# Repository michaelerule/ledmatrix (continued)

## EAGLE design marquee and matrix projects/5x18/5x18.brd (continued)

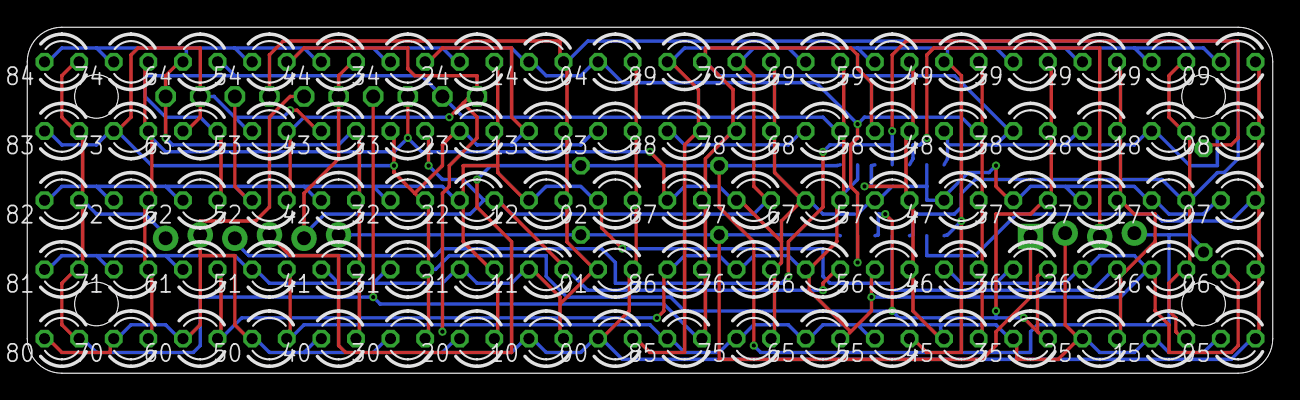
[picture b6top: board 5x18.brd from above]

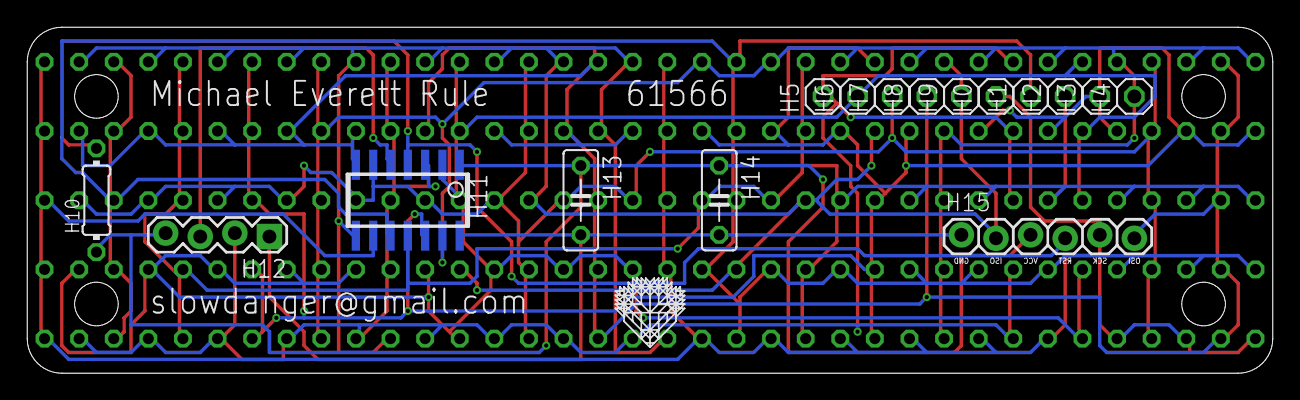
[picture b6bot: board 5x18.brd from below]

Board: 2 copper layers, 91.4 x 25.4 mm, 107 parts (17 on the bottom side), 14 nets.

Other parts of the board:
H16: LOGO

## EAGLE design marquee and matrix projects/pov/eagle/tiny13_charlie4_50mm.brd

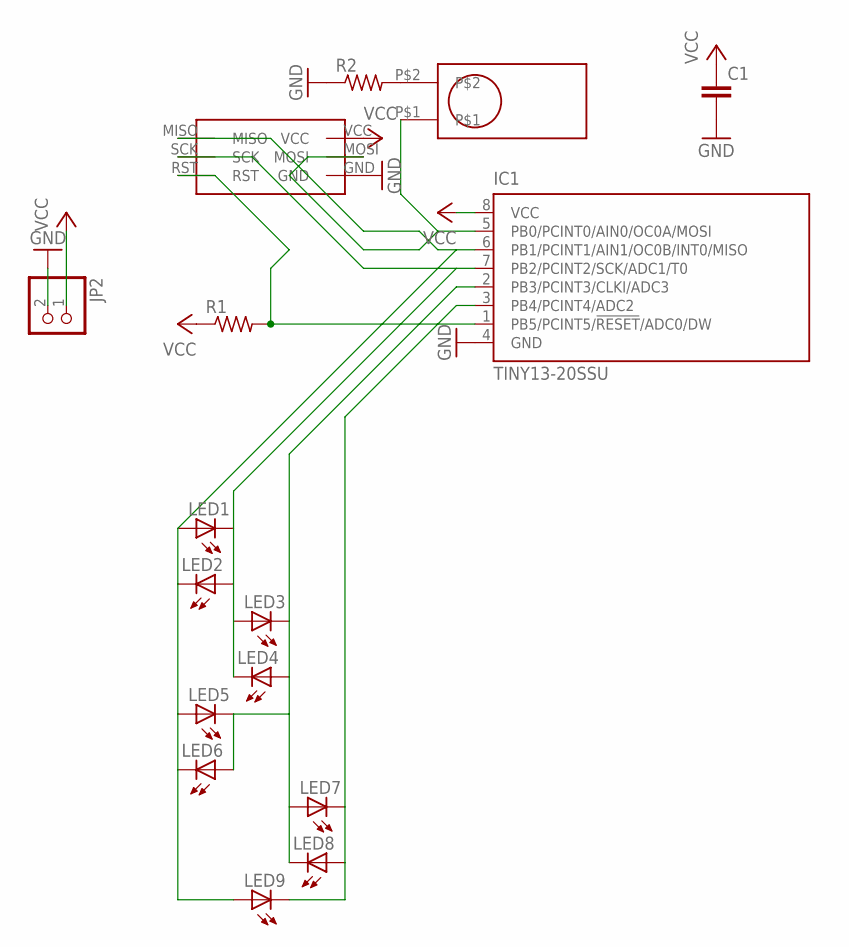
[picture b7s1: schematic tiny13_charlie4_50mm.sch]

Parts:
C1: C-EU025-025X050; C025-025X050
IC1: TINY13-20SSU; 8S1
JP2: PINHD-1X2/90; 1X02/90
LED1, LED2, LED3, LED4, LED5, LED6, LED7, LED8, LED9: LED3MM
R1, R2: R-US_0207/7; 0207/7
U$1: TILT_SWITCH_MECHANICAL
U$2: AVR_ISP_6_PIN_1X6_SMT_CONTACT_PROGRAMMER; CONTACT_ISP_PROGRAMMER_1X6_ATMEL

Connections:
GND: C1.2, IC1.4 (GND), JP2.2, R2.1, U$2.GND
unnamed: IC1.2 (PB3/PCINT3/CLKI/ADC3), LED3.K (C), LED4.A, LED5.K (C), LED6.A, LED7.A, LED8.K (C)
unnamed: IC1.7 (PB2/PCINT2/SCK/ADC1/T0), LED1.K (C), LED2.A, LED3.A, LED4.K (C), U$2.SCK
unnamed: R2.2, U$1.P$2
unnamed: IC1.3 (PB4/PCINT4/ADC2), LED7.K (C), LED8.A, LED9.K (C)
unnamed: IC1.5 (PB0/PCINT0/AIN0/OC0A/MOSI), U$1.P$1, U$2.MOSI
unnamed: IC1.1 (PB5/PCINT5/!RESET!/ADC0/DW), R1.2, U$2.RST
unnamed: IC1.6 (PB1/PCINT1/AIN1/OC0B/INT0/MISO), LED1.A, LED2.K (C), LED5.A, LED6.K (C), LED9.A, U$2.MISO
VCC: C1.1, IC1.8 (VCC), JP2.1, R1.1, U$2.VCC

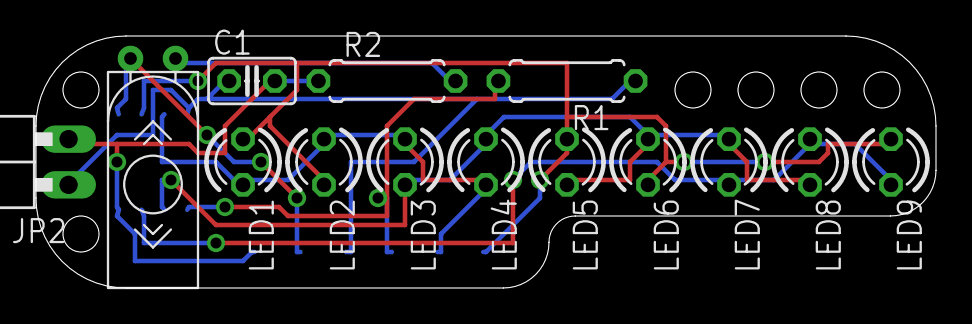
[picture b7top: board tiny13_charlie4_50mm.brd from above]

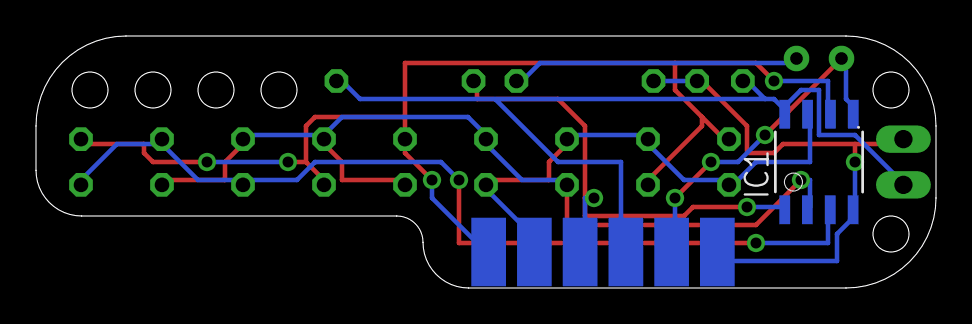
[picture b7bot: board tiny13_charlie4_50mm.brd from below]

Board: 2 copper layers, 50.0 x 14.0 mm, 16 parts (2 on the bottom side), 9 nets.

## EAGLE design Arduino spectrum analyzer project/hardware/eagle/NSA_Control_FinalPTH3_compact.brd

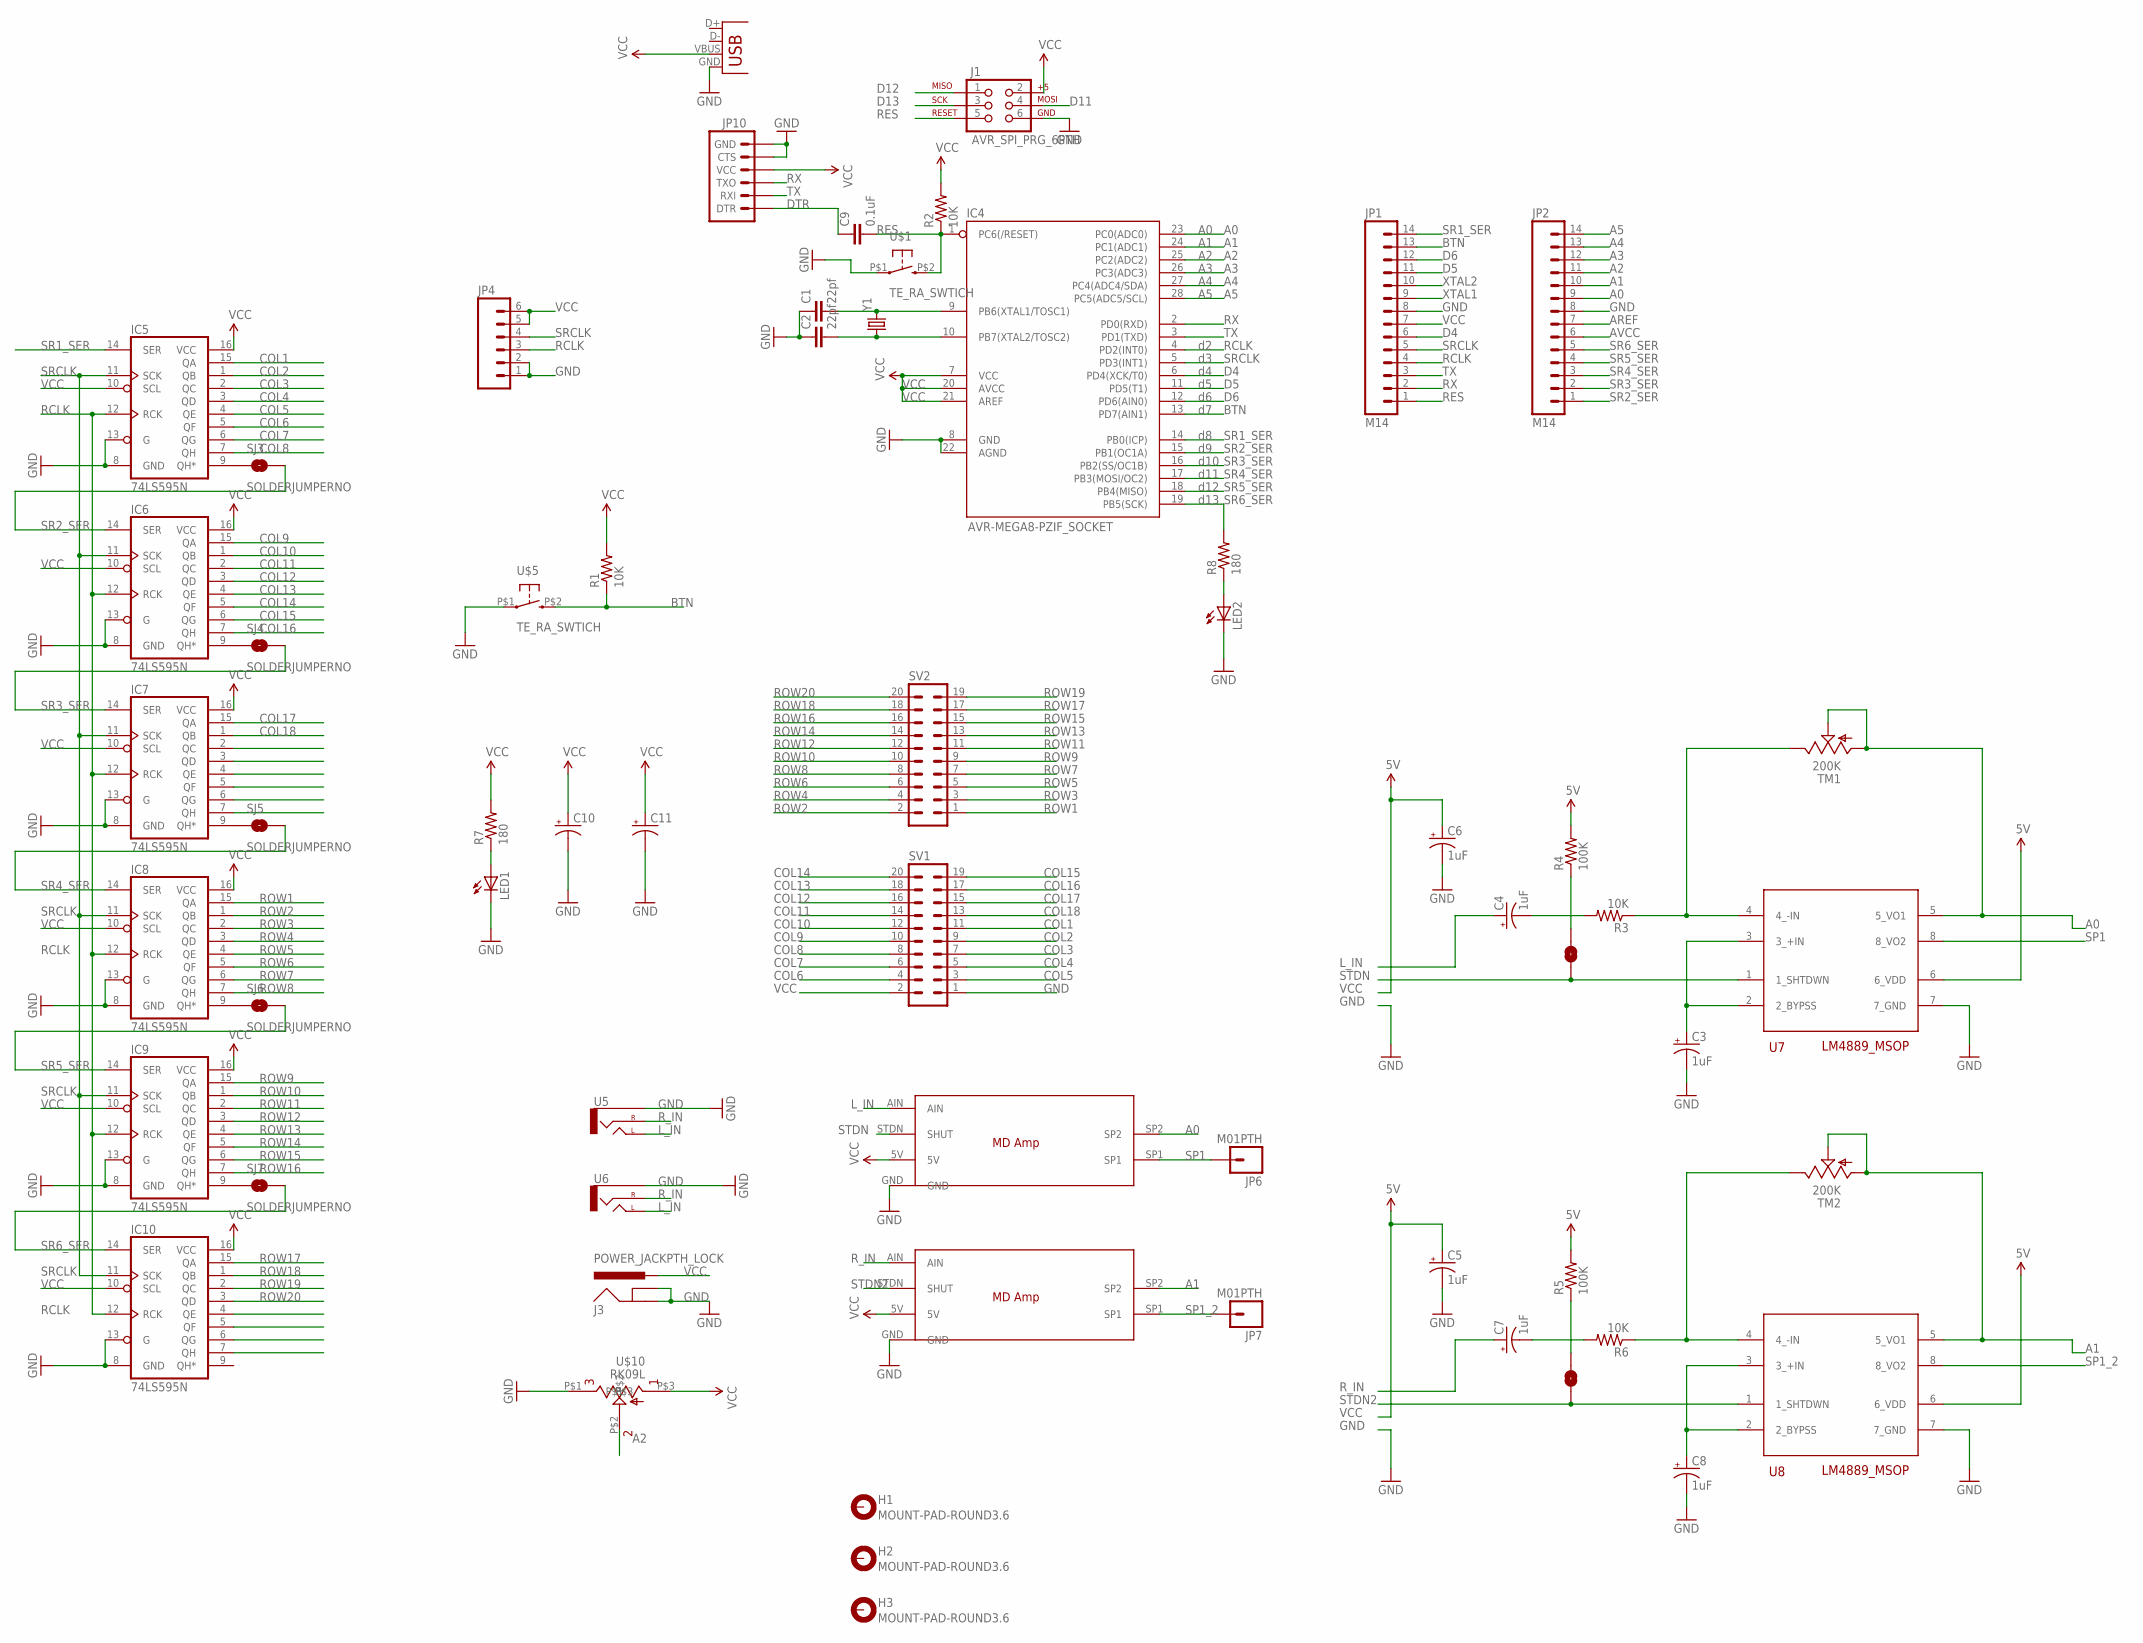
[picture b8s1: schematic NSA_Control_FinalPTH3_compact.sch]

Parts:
C1, C2: 22pf; CAP-PTH-SMALL
C3, C4, C5, C6, C7, C8: 1uF; EIA3216-KIT
C9: 0.1uF; CAP-PTH-SMALL
C10, C11: CPOL-USE5-8.5; E5-8,5
H1, H2, H3: MOUNT-PAD-ROUND3.6; 3,6-PAD
IC4: AVR-MEGA8-PZIF_SOCKET; DIL28-3-ZIF_SOCKET
IC5, IC6, IC7, IC8, IC9, IC10: 74LS595N; DIL16
J1: AVR_SPI_PRG_6PTH; 2X3
J3: POWER_JACKPTH_LOCK; POWER_JACK_PTH_LOCK
JP1, JP2: M14; 1X14
JP4: M06LONGPADS; 1X06_LONGPADS
JP6, JP7: M01PTH; 1X01
JP10: ARDUINO_SERIAL_PROGRAMLOCK; 1X06_LOCK
LED1, LED2: LED5MM
R1, R2: 10K; AXIAL-0.4
R3, R6: 10K; 1206
R4, R5: 100K; 1206
R7, R8: 180; AXIAL-0.4
SJ1, SJ2: SOLDERJUMPERNC; SJ_2S
SJ3, SJ4, SJ5, SJ6, SJ7: SOLDERJUMPERNO; SJ_2S-NO
SV1, SV2: ML20
TM1, TM2: 200K; 6MM
U5, U6: AUDIO-JACKPTH; AUDIO-JACK
U7, U8: LM4889_MSOP; MSOP8
U$1, U$5: TE_RA_SWTICH; TE_RA_SWITCH
U$6, U$7: MD_AMP
U$10: RK09L
X1: USBSMD; USB-MINIB
Y1: CRYSTALHC49UV; HC49U-V

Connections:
6V: R4.2, R5.2, U7.6 (6_VDD), U8.6 (6_VDD)
A0: IC4.23 (PC0(ADC0)), JP2.9, TM1.A, TM1.S, U7.5 (5_VO1), U$6.SP2
A1: IC4.24 (PC1(ADC1)), JP2.10, TM2.A, TM2.S, U8.5 (5_VO1), U$7.SP2
A2: IC4.25 (PC2(ADC2)), JP2.11, U$10.P$2
A3: IC4.26 (PC3(ADC3)), JP2.12
A4: IC4.27 (PC4(ADC4/SDA)), JP2.13
A5: IC4.28 (PC5(ADC5/SCL)), JP2.14
AREF: JP2.7
AVCC: JP2.6
BTN: IC4.13 (PD7(AIN1)), JP1.13, R1.P$1 (1), U$5.P$2 (3)
COL1: IC5.15 (QA), SV1.11
COL2: IC5.1 (QB), SV1.9
COL3: IC5.2 (QC), SV1.7
COL4: IC5.3 (QD), SV1.5
COL5: IC5.4 (QE), SV1.3
COL6: IC5.5 (QF), SV1.4
COL7: IC5.6 (QG), SV1.6
COL8: IC5.7 (QH), SV1.8
COL9: IC6.15 (QA), SV1.10
COL10: IC6.1 (QB), SV1.12
COL11: IC6.2 (QC), SV1.14
COL12: IC6.3 (QD), SV1.16
COL13: IC6.4 (QE), SV1.18
COL14: IC6.5 (QF), SV1.20
COL15: IC6.6 (QG), SV1.19
COL16: IC6.7 (QH), SV1.17
COL17: IC7.15 (QA), SV1.15
COL18: IC7.1 (QB), SV1.13
D4: IC4.6 (PD4(XCK/T0)), JP1.6
D5: IC4.11 (PD5(T1)), JP1.11
D6: IC4.12 (PD6(AIN0)), JP1.12
D11: J1.4
D12: J1.1
D13: J1.3
DTR: C9.1, JP10.1 (DTR)
GND: C1.1, C2.1, C3.C (-), C5.C (-), C6.C (-), C8.C (-), C10.-, C11.-, IC4.8 (GND), IC4.22 (AGND), IC5.8 (GND), IC5.13 (G), IC6.8 (GND), IC6.13 (G), IC7.8 (GND), IC7.13 (G), IC8.8 (GND), IC8.13 (G), IC9.8 (GND), IC9.13 (G), IC10.8 (GND), IC10.13 (G), J1.6, J3.GND, J3.GNDBREAK, JP1.8, JP2.8, JP4.1, JP4.2, JP10.5 (CTS), JP10.6 (GND), LED1.K (C), LED2.K (C), SV1.1, U5.SLEEVE, U6.SLEEVE, U7.7 (7_GND), U8.7 (7_GND), U$1.P$1 (1), U$5.P$1 (1), U$6.GND, U$7.GND, U$10.P$1, X1.GND
L_IN: C4.A (+), U5.TIP (LEFT), U6.TIP (LEFT), U$6.AIN
unnamed: LED1.A, R7.P$1 (1)
unnamed: LED2.A, R8.P$1 (1)
unnamed: C8.A (+), U8.2 (2_BYPSS), U8.3 (3_+IN)
unnamed: IC5.9 (QH*), SJ3.1
unnamed: IC6.9 (QH*), SJ4.1
unnamed: C3.A (+), U7.2 (2_BYPSS), U7.3 (3_+IN)
unnamed: R6.1, TM2.E, U8.4 (4_-IN)
unnamed: R3.1, TM1.E, U7.4 (4_-IN)
unnamed: C4.C (-), R3.2
unnamed: C7.C (-), R6.2
unnamed: R4.1, SJ1.2
unnamed: R5.1, SJ2.2
unnamed: IC7.9 (QH*), SJ5.1
unnamed: IC8.9 (QH*), SJ6.1
unnamed: IC9.9 (QH*), SJ7.1
RCLK: IC4.4 (PD2(INT0)), IC5.12 (RCK), IC6.12 (RCK), IC7.12 (RCK), IC8.12 (RCK), IC9.12 (RCK), IC10.12 (RCK), JP1.4, JP4.3
RES: C9.2, IC4.1 (PC6(/RESET)), J1.5, JP1.1, R2.P$1 (1), U$1.P$2 (3)
ROW1: IC8.15 (QA), SV2.1
ROW2: IC8.1 (QB), SV2.2
ROW3: IC8.2 (QC), SV2.3
ROW4: IC8.3 (QD), SV2.4
ROW5: IC8.4 (QE), SV2.5
ROW6: IC8.5 (QF), SV2.6
ROW7: IC8.6 (QG), SV2.7
ROW8: IC8.7 (QH), SV2.8
ROW9: IC9.15 (QA), SV2.9
ROW10: IC9.1 (QB), SV2.10
ROW11: IC9.2 (QC), SV2.11
ROW12: IC9.3 (QD), SV2.12
ROW13: IC9.4 (QE), SV2.13
ROW14: IC9.5 (QF), SV2.14
ROW15: IC9.6 (QG), SV2.15
ROW16: IC9.7 (QH), SV2.16
ROW17: IC10.15 (QA), SV2.17
ROW18: IC10.1 (QB), SV2.18
ROW19: IC10.2 (QC), SV2.19
ROW20: IC10.3 (QD), SV2.20
RX: IC4.2 (PD0(RXD)), JP1.2, JP10.3 (TXO)
R_IN: C7.A (+), U5.RING (RIGHT), U6.RING (RIGHT), U$7.AIN
SP1: JP6.1, U7.8 (8_VO2), U$6.SP1
SP1_2: JP7.1, U8.8 (8_VO2), U$7.SP1
SR1_SER: IC4.14 (PB0(ICP)), IC5.14 (SER), JP1.14
SR2_SER: IC4.15 (PB1(OC1A)), IC6.14 (SER), JP2.1, SJ3.2
SR3_SER: IC4.16 (PB2(SS/OC1B)), IC7.14 (SER), JP2.2, SJ4.2
SR4_SER: IC4.17 (PB3(MOSI/OC2)), IC8.14 (SER), JP2.3, SJ5.2
SR5_SER: IC4.18 (PB4(MISO)), IC9.14 (SER), JP2.4, SJ6.2
SR6_SER: IC4.19 (PB5(SCK)), IC10.14 (SER), JP2.5, R8.P$2 (2), SJ7.2
SRCLK: IC4.5 (PD3(INT1)), IC5.11 (SCK), IC6.11 (SCK), IC7.11 (SCK), IC8.11 (SCK), IC9.11 (SCK), IC10.11 (SCK), JP1.5, JP4.4
STDN: SJ1.1, U7.1 (1_SHTDWN), U$6.STDN (SHUT)
STDN2: SJ2.1, U8.1 (1_SHTDWN), U$7.STDN (SHUT)
TX: IC4.3 (PD1(TXD)), JP1.3, JP10.2 (RXI)
VCC: C5.A (+), C6.A (+), C10.+, C11.+, IC4.7 (VCC), IC4.20 (AVCC), IC4.21 (AREF), IC5.10 (SCL), IC5.16 (VCC), IC6.10 (SCL), IC6.16 (VCC), IC7.10 (SCL), IC7.16 (VCC), IC8.10 (SCL), IC8.16 (VCC), IC9.10 (SCL), IC9.16 (VCC), IC10.10 (SCL), IC10.16 (VCC), J1.2, J3.PWR, JP1.7, JP4.5, JP4.6, JP10.4 (VCC), R1.P$2 (2), R2.P$2 (2), R7.P$2 (2), SV1.2, U$6.5V, U$7.5V, U$10.P$3, X1.VBUS
XTAL1: C1.2, IC4.9 (PB6(XTAL1/TOSC1)), JP1.9, Y1.2
XTAL2: C2.2, IC4.10 (PB7(XTAL2/TOSC2)), JP1.10, Y1.1

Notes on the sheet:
d10
d11
d12
d13

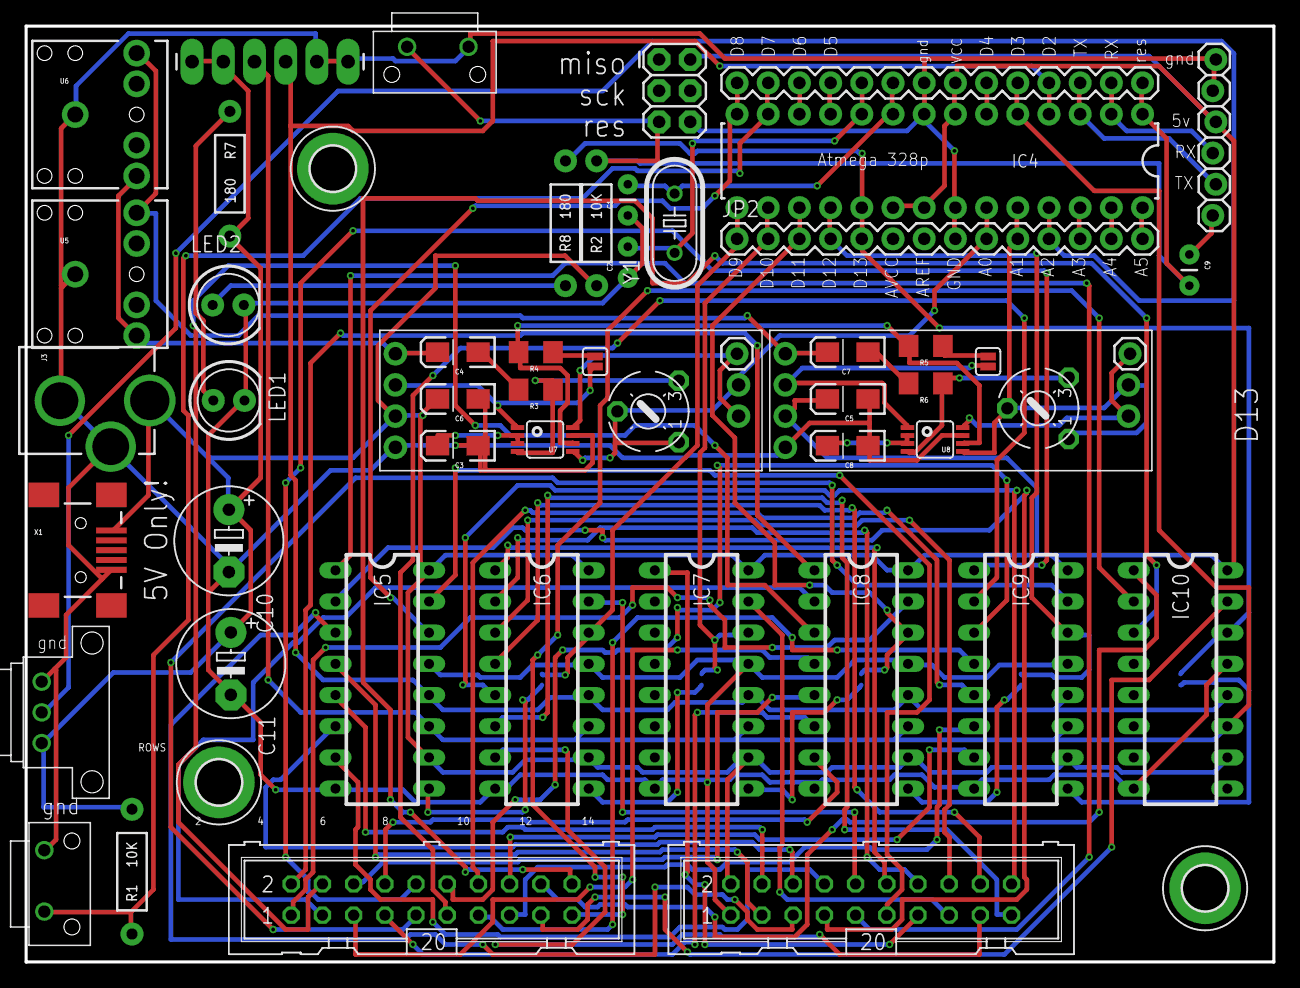
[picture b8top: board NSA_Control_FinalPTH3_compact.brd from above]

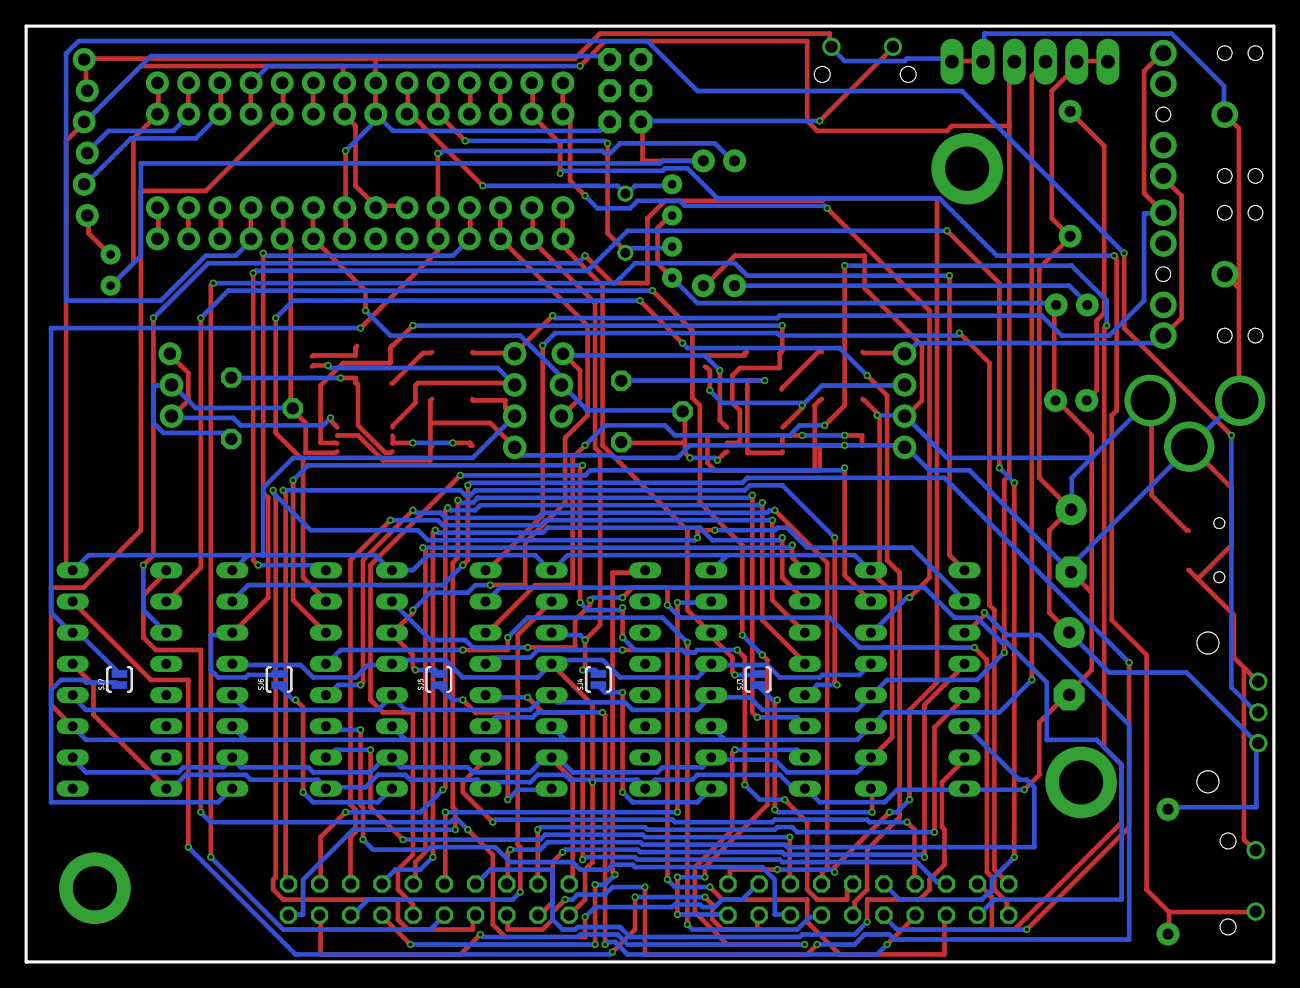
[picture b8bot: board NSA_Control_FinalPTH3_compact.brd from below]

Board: 2 copper layers, 101.6 x 76.2 mm, 61 parts (5 on the bottom side), 86 nets.

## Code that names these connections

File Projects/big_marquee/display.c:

/*
Hardware notes
===============================================================================

-U lfuse:w:0xe4:m

DDRx   : 1 = output, 0 = input
PORTx : output buffer
PINx  : digital input buffer ( writes set pullups )
                          ______
         !RESET     PC6 -|  U  |- PC5
                    PD0 -|     |- PC4
                    PD1 -|     |- PC3
                    PD2 -|     |- PC2
                    PD3 -|  m  |- PC1
                    PD4 -|  *  |- PC0
                    VCC -|  8  |- GND
                    GND -|     |- AREF
                    PB6 -|     |- AVCC
                    PB7 -|     |- PB5   SCK  ( yellow )
                    PD5 -|     |- PB4   MISO ( green )
                    PD6 -|     |- PB3   MOSI ( blue )
                    PD7 -|     |- PB2
                    PB0 -|_____|- PB1

        Programmer pinout, 6 pin:
                o
        6 MISO +-+  VCC 3
        5 SCK  + + MOSI 2 
        4 RST  +-+  GND 1
        
        Programmer pinout, 6 pin, linear:
                
        6 MISO +  
        5 SCK  + 
        4 RST  +  
        VCC 3  +
        MOSI 2 +
        GND 1  +

        Programmer pinout, 10 pin:
                
        3 vcc  +-+   MOSI 2
               + +    
               + +]  RST  4 
               + +   SCK  5 
        1 gnd  +-+   MISO 6
        
    PORT : write to here to set output
    DDR  : write to here to set IO. 1 for output.
    PIN  : pull ups ? digital input ?

thanks to http://brownsofa.org/blog/archives/215 for explaining timer interrupts

avrdude -c avrispmkII -p m48 -B100 -P /dev/ttyUSB0 -U lfuse:w:0xE2:m 
avrdude -c avrispmkII -p m48 -B1000 -P /dev/ttyUSB0 -F


#./blues.py | tee blues.c &&\
#./scale.py | tee scale.c &&\
#./chromatic_up.py | tee chromatic_up.c &&\
#./chromatic_down.py | tee chromatic_down.c &&\
avr-gcc -Os -mmcu=atmega48 ./display.c -o a.o &&\
avr-objcopy -j .text -j .data -O binary a.o a.bin  && du -b ./a.bin &&\
avrdude -F -c avrispmkII -p m48 -B1 -P /dev/ttyUSB0 -F -U flash:w:a.bin


*/

#include <avr/io.h>
#include <avr/interrupt.h>
#include <avr/pgmspace.h>

#define N 8
#define ONE ((uint32_t)1)
//SERIAL MACROS
#define DATA_AVAILABLE (UCSRA&(1<<RXC))
#define OK_TO_SEND (UCSRA & (1 << UDRE))
#define NOP __asm__("nop\n\t")
#define once(condition) {while(!(condition));}

//#include "alphabet.c"

void setDDR(uint32_t ddr) 
{
    DDRD = ddr & 0xff;
    ddr >>= 8;
    DDRC = ddr & 0xff;
    ddr >>= 8;
    DDRB = ddr & 0xff;
}

void setPort(uint32_t pins)
{
    PORTD = pins & 0xff;
    pins >>= 8;
    PORTC = pins & 0xff;
    pins >>= 8;
    PORTB = pins & 0xff;
}

void delay(uint32_t n)
{
    while (n--) NOP;
}

//PIN POSITIONS ON DISPLAY
#define d0 0
#define d1 1
#define d2 2
#define d3 3
#define d4 4
#define d5 5
#define d6 6
#define d7 7
#define c0 8
#define c1 9 
#define c2 10
#define c3 11
#define c4 12
#define c5 13
#define c6 14
#define c7 15
#define b0 16
#define b1 17
#define b2 18
#define b3 19
#define b4 20
#define b5 21
#define b6 22
#define b7 23
const uint8_t anodes[2*N]   PROGMEM = {c4,c1,d4,c0,b3,d5,b0,b1,b2,d7,b4,d6,c5,b5,c2,c3};
const uint8_t cathodes[2*N] PROGMEM = {b2,c2,c3,b5,c5,b4,d7,d6,c4,b0,b1,d5,b3,d4,c1,c0};

#define READ(x) ((uint8_t)(pgm_read_byte_near(&x)))

int main()
{   
    // ENABLE SERIAL
    UCSRB = 0x18;
    UCSRC = 0x86;
    UBRRL = 0x33;

    uint8_t r,c;
    uint8_t disp[16];
    
    while(1)
    for (r=0;r<16;r++)
    for (c=0;c<8;c++) {
        // SCAN DISPLAY
        uint32_t C = ONE<<READ(cathodes[r]);
        uint32_t A = ONE<<READ(anodes[r>=8?c+8:c]);
        setDDR(0);
        setPort(A);
        if ((disp[r]>>c)&1) setDDR(C|A);
        delay(50);
        
        //HANDLE NEW DATA IF PRESENT
        if (DATA_AVAILABLE)
        {
            uint8_t x = UDR;
            once(OK_TO_SEND) 
                UDR = disp[15]; // SDO
            uint8_t i;
            for (i=15;i>=1;i--)
                disp[i]=disp[i-1];
            disp[0]=x;
        }
    }
} 

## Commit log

2017-07-27 initialize repo
2017-07-27 reorganize into projects vs tools
2017-07-27 minor refactor
2019-02-10 organized pixel fonts
2019-02-21 remove tinymarquee files; these are stored in a separate repository
2019-02-21 clean up bigmarquee project files a bit
2019-02-21 update contact information
2019-02-21 more descriptive project names; remove some empty documentation folders
2019-02-21 removed some empty folders
2019-02-21 simplify readme
